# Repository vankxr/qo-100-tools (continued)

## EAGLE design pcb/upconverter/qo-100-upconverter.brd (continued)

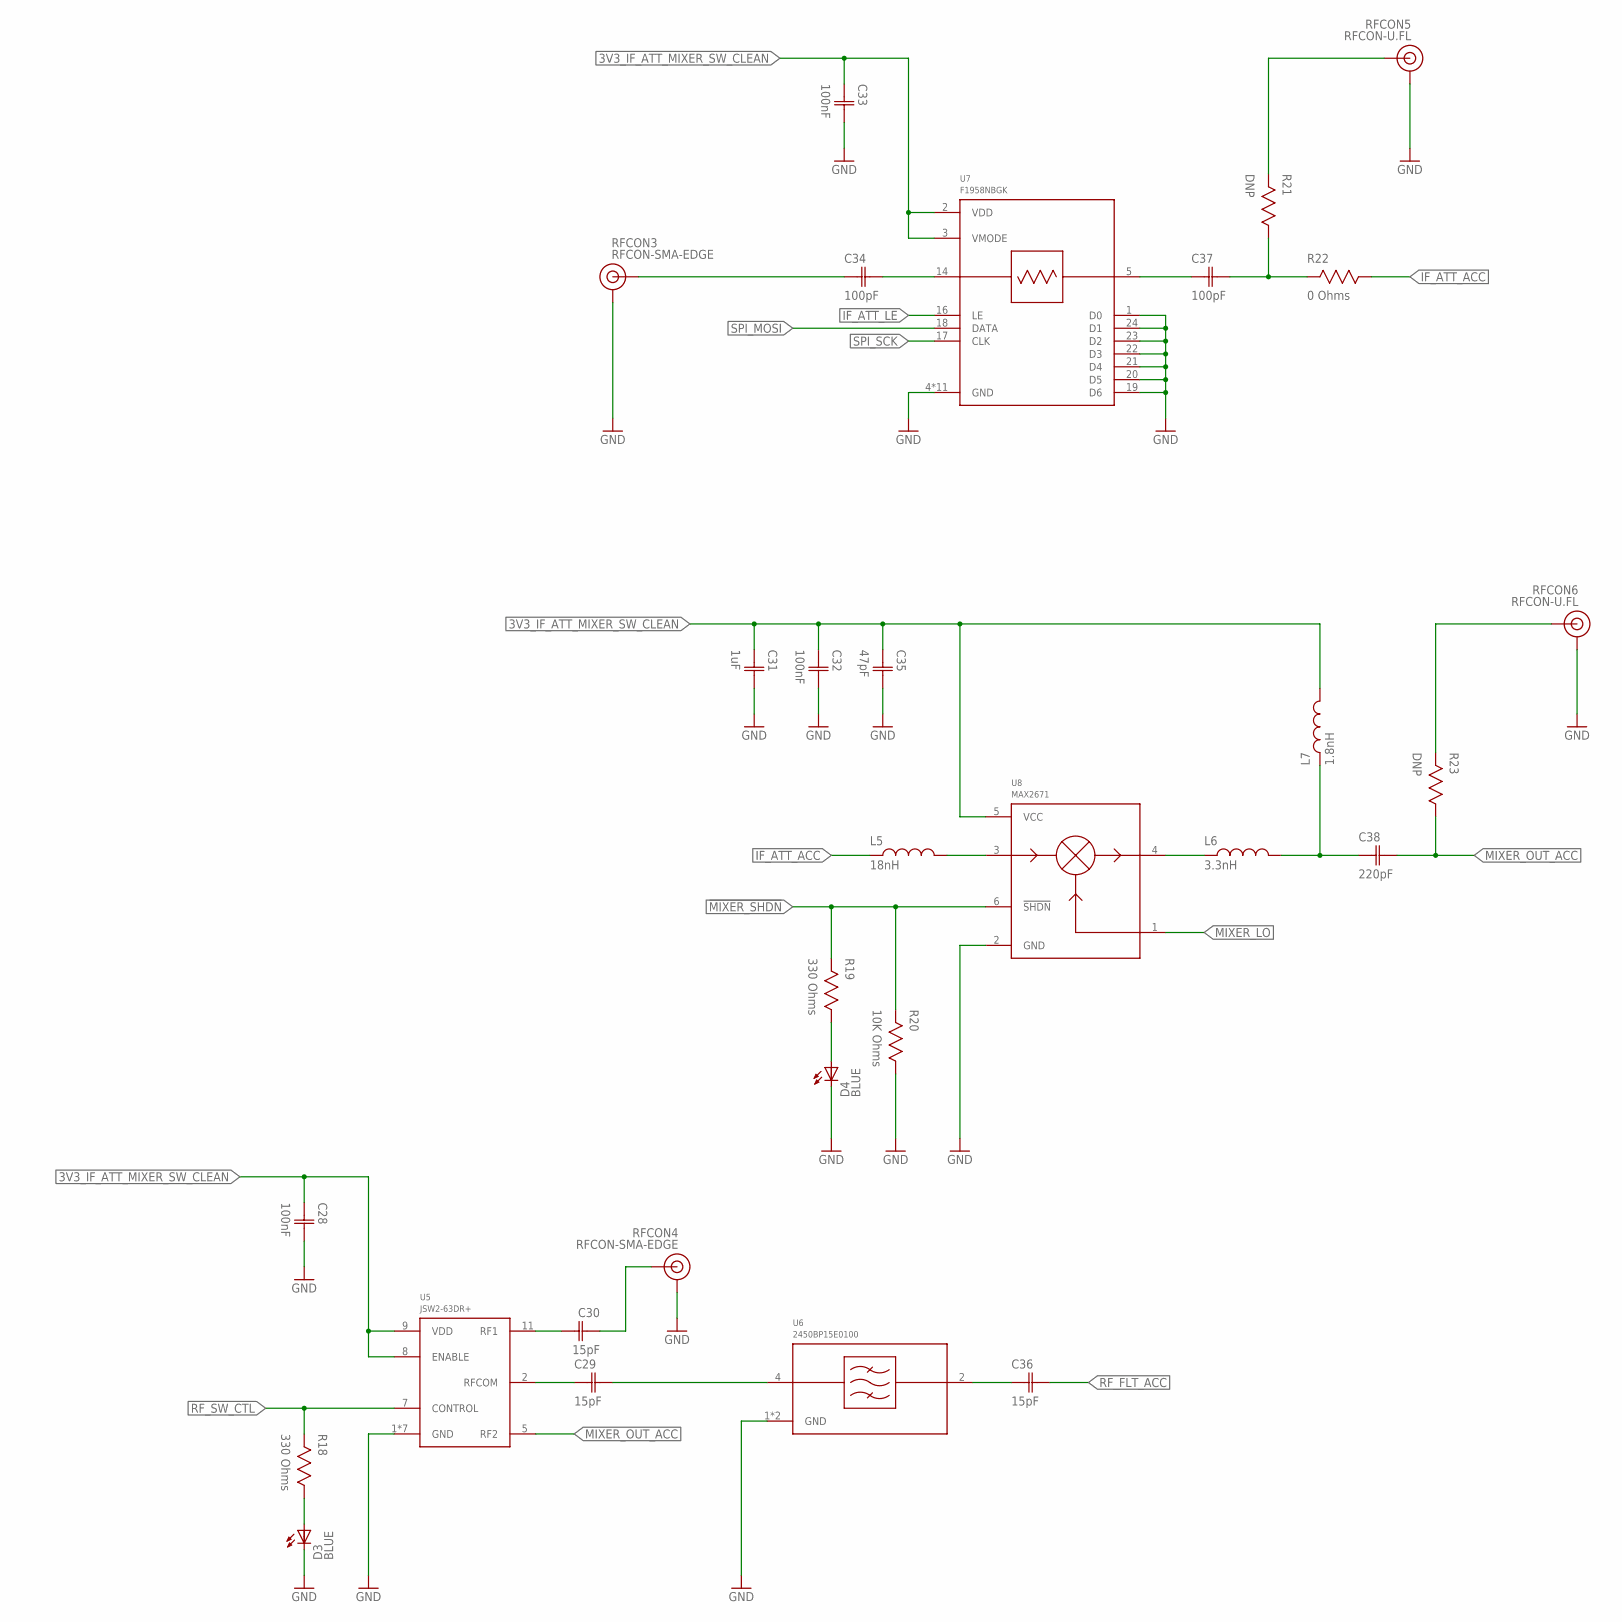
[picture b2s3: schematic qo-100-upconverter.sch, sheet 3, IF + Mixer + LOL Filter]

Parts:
C28, C32, C33: 100nF; CAP0603
C29, C30, C36: 15pF; CAP0603
C31: 1uF; CAP0603
C34, C37: 100pF; CAP0603
C35: 47pF; CAP0603
C38: 220pF; CAP0603
D3, D4: LED0603; 0603
L5: 18nH; IND0603
L6: 3.3nH; IND0603
L7: 1.8nH; IND0603
R18, R19: 330 Ohms; RES0603
R20: 10K Ohms; RES0603
R21, R23: DNP; RES0603
R22: 0 Ohms; RES0603
RFCON3, RFCON4: RFCON-SMA-EDGE; SMA-EDGE
RFCON5, RFCON6: RFCON-U.FL; U.FL
U5: JSW2-63DR+; MT1818
U6: 2450BP15E0100
U7: F1958NBGK; QFN24_2
U8: MAX2671; SOT23-6

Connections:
3V3_IF_ATT_MIXER_SW_CLEAN: C28.1 (C1), C31.1 (C1), C32.1 (C1), C33.1 (C1), C35.1 (C1), L7.2, U5.8 (ENABLE), U5.9 (VDD), U7.2 (VDD), U7.3 (VMODE), U8.5 (VCC); also elsewhere on the board
!MIXER_SHDN: R19.2, R20.2, U8.6 (!SHDN); also elsewhere on the board
GND: C28.2 (C2), C31.2 (C2), C32.2 (C2), C33.2 (C2), C35.2 (C2), D3.C, D4.C, R20.1, RFCON3.GND@0 (GND), RFCON3.GND@1 (GND), RFCON3.GND@2 (GND), RFCON3.GND@3 (GND), RFCON4.GND@0 (GND), RFCON4.GND@1 (GND), RFCON4.GND@2 (GND), RFCON4.GND@3 (GND), RFCON5.P$1 (GND), RFCON5.P$2 (GND), RFCON6.P$1 (GND), RFCON6.P$2 (GND), U5.1 (GND), U5.3 (GND), U5.4 (GND), U5.6 (GND), U5.10 (GND), U5.12 (GND), U5.17 (GND), U6.1 (GND), U6.3 (GND), U7.1 (D0), U7.4 (GND), U7.6 (GND), U7.7 (GND), U7.8 (GND), U7.9 (GND), U7.10 (GND), U7.11 (GND), U7.12 (GND), U7.13 (GND), U7.15 (GND), U7.19 (D6), U7.20 (D5), U7.21 (D4), U7.22 (D3), U7.23 (D2), U7.24 (D1), U7.25 (GND), U8.2 (GND); also elsewhere on the board
IF_ATT_ACC: L5.1, R22.1
IF_ATT_ACC_PROBE: C37.2 (C2), R21.1, R22.2
IF_ATT_DCC: C37.1 (C1), U7.5 (RF1)
IF_ATT_LE: U7.16 (LE); also elsewhere on the board
IF_IN_ACC: C34.2 (C2), U7.14 (RF2)
IF_IN_DCC: C34.1 (C1), RFCON3.SIG (SIGNAL)
MIXER_IN_DCC: L5.2, U8.3 (IFIN)
MIXER_LO: U8.1 (LO); also elsewhere on the board
MIXER_OUT_ACC: C38.2 (C2), R23.1, U5.5 (RF2)
MIXER_OUT_DCC: L6.1, U8.4 (RFOUT)
unnamed: D4.A, R19.1
unnamed: C38.1 (C1), L6.2, L7.1
unnamed: D3.A, R18.1
unnamed: R21.2, RFCON5.P$3 (SIGNAL)
unnamed: R23.2, RFCON6.P$3 (SIGNAL)
RF_FLT_ACC: C36.2 (C2); also elsewhere on the board
RF_IN_ACC: C30.2 (C2), U5.11 (RF1)
RF_IN_DCC: C30.1 (C1), RFCON4.SIG (SIGNAL)
RF_SEL_ACC: C29.2 (C2), U6.4 (RFIN)
RF_SEL_DCC: C29.1 (C1), U5.2 (RFCOM)
RF_SEL_FILT_DCC: C36.1 (C1), U6.2 (RFOUT)
RF_SW_CTL: R18.2, U5.7 (CONTROL); also elsewhere on the board
SPI_MOSI: U7.18 (DATA); also elsewhere on the board
SPI_SCK: U7.17 (CLK); also elsewhere on the board

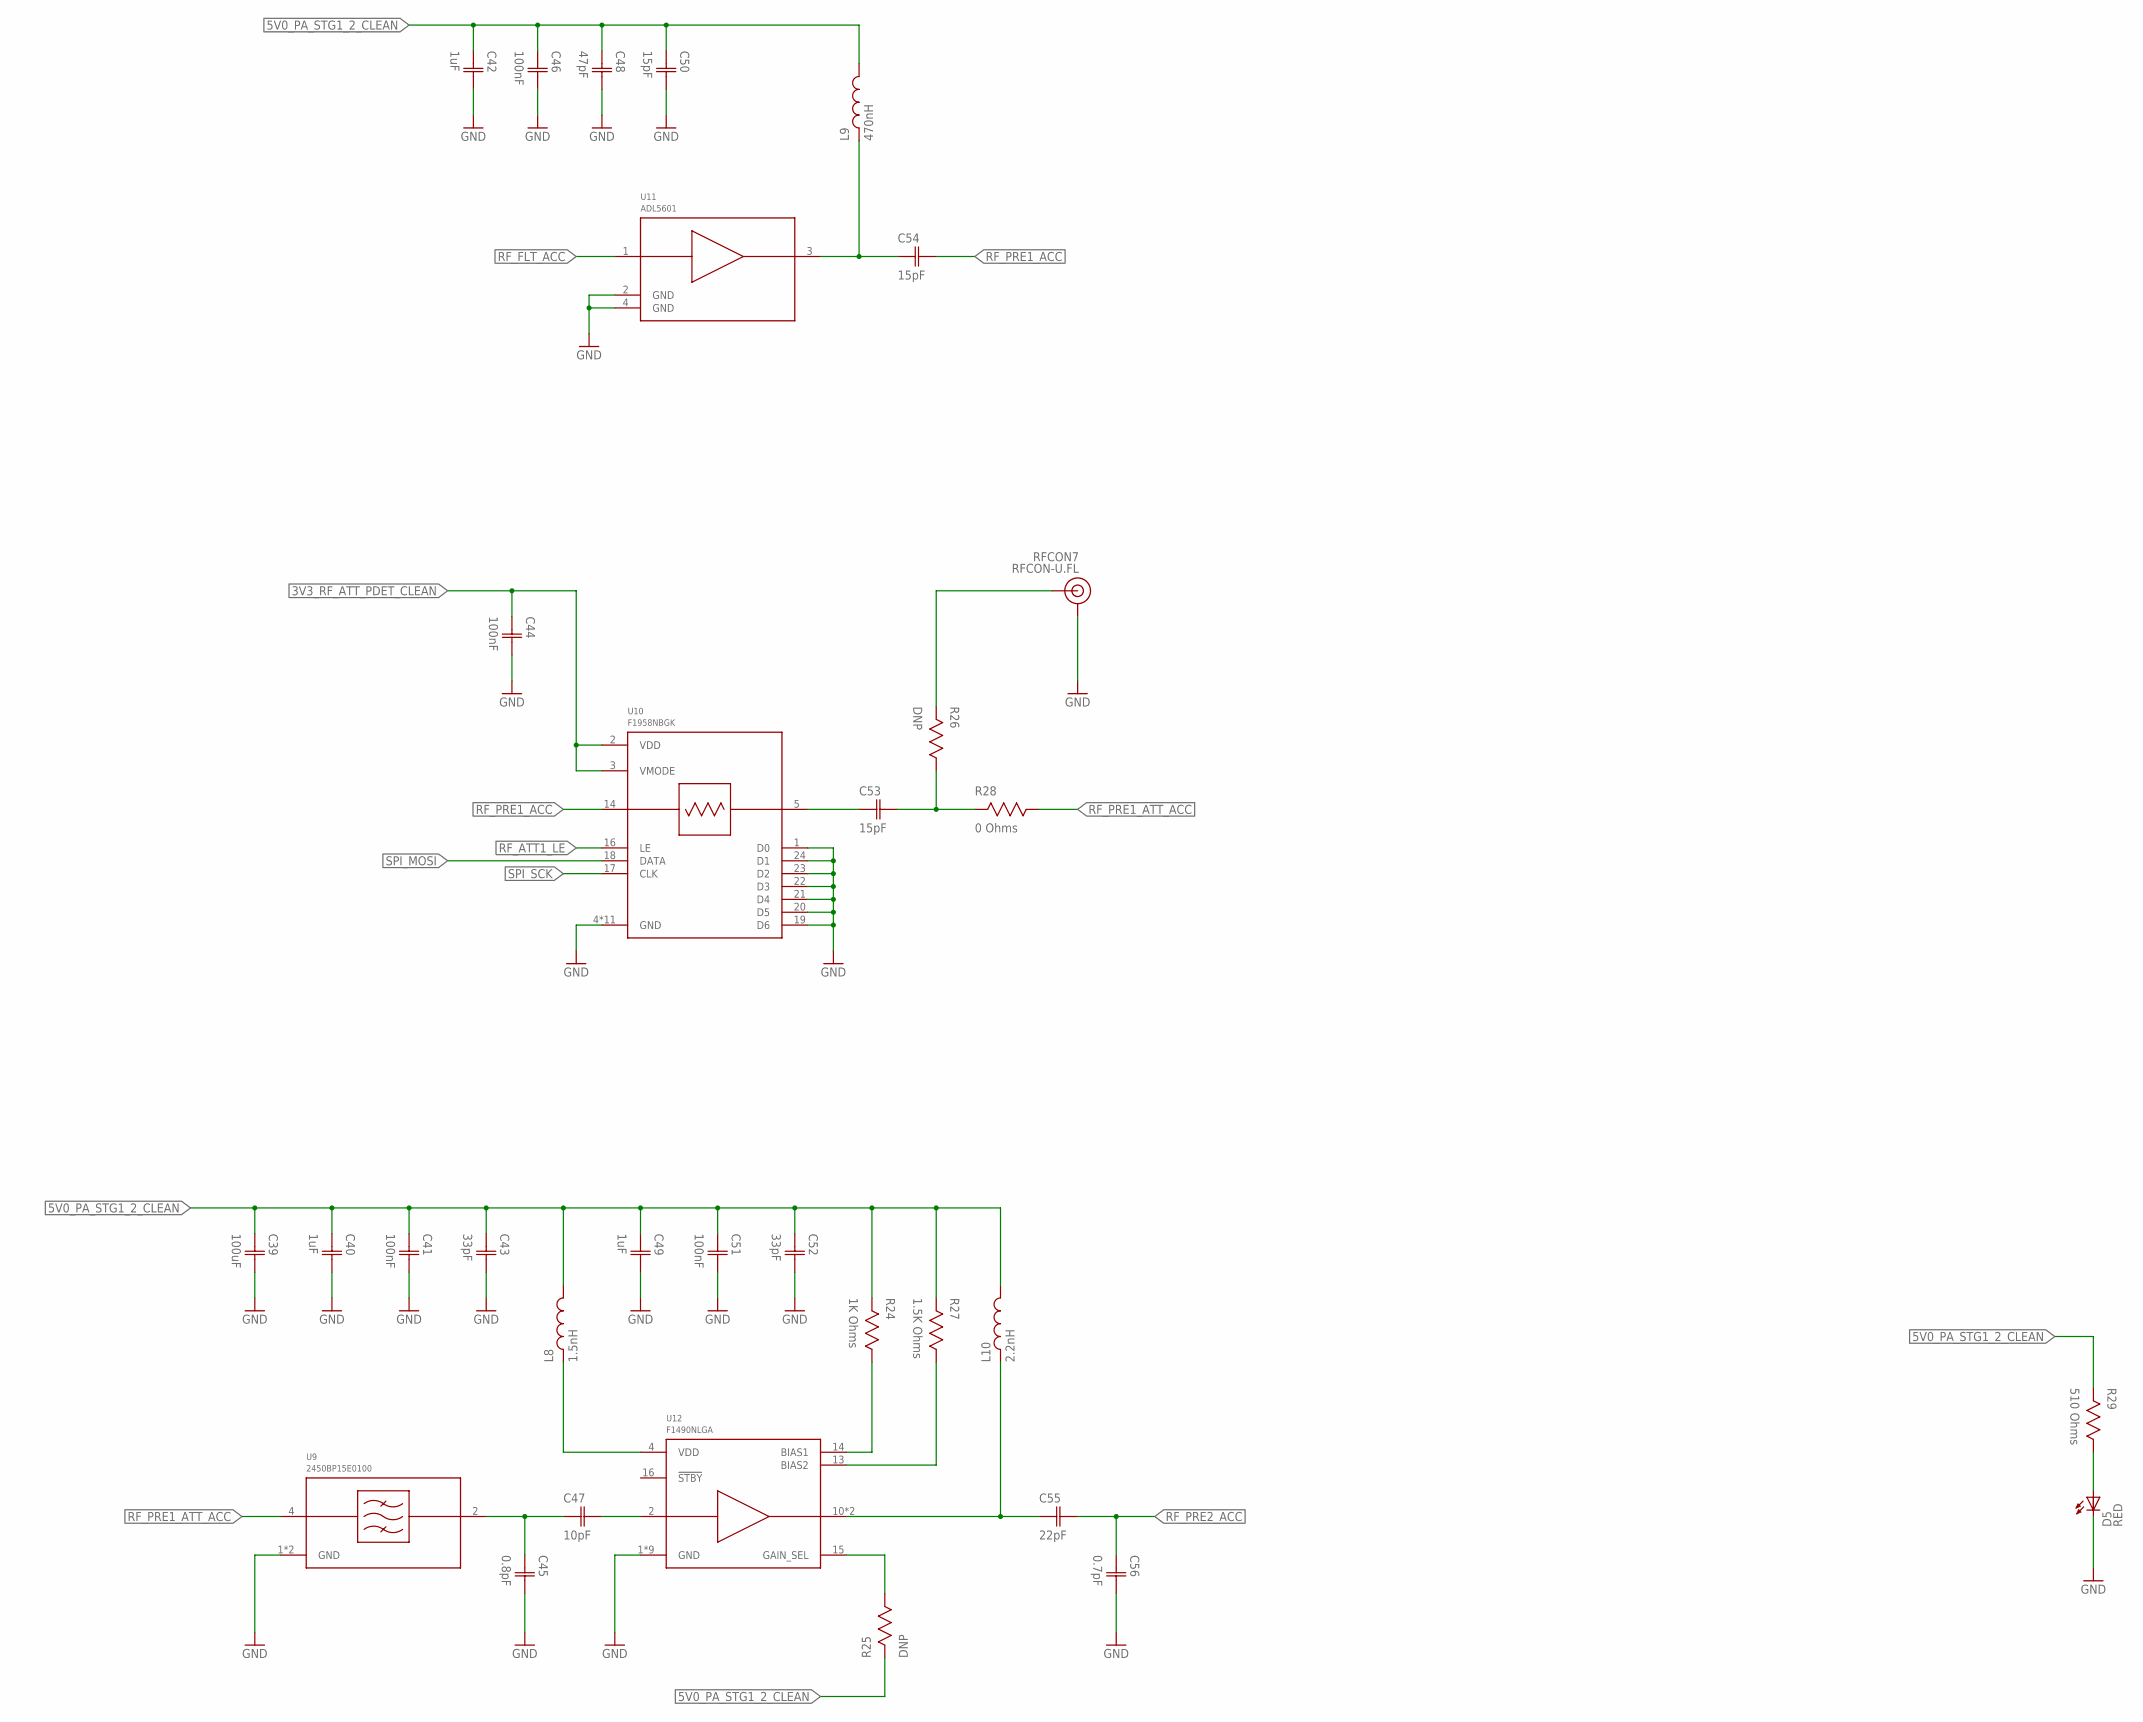
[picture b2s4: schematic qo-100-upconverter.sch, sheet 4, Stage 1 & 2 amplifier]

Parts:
C39: 100uF; CAP1206
C40, C42, C49: 1uF; CAP0603
C41, C44, C46, C51: 100nF; CAP0603
C43, C52: 33pF; CAP0603
C45: 0.8pF; CAP0603
C47: 10pF; CAP0603
C48: 47pF; CAP0603
C50, C53, C54: 15pF; CAP0603
C55: 22pF; CAP0603
C56: 0.7pF; CAP0603
D5: LED0603; 0603
L8: 1.5nH; IND0603
L9: 470nH; IND0603
L10: 2.2nH; IND0603
R24: 1K Ohms; RES0603
R25, R26: DNP; RES0603
R27: 1.5K Ohms; RES0603
R28: 0 Ohms; RES0603
R29: 510 Ohms; RES0603
RFCON7: RFCON-U.FL; U.FL
U9: 2450BP15E0100
U10: F1958NBGK; QFN24_2
U11: ADL5601; SOT89
U12: F1490NLGA; QFN16

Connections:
3V3_RF_ATT_PDET_CLEAN: C44.1 (C1), U10.2 (VDD), U10.3 (VMODE); also elsewhere on the board
5V0_PA_STG1_2_CLEAN: C39.1 (C1), C40.1 (C1), C41.1 (C1), C42.1 (C1), C43.1 (C1), C46.1 (C1), C48.1 (C1), C49.1 (C1), C50.1 (C1), C51.1 (C1), C52.1 (C1), L8.2, L9.2, L10.2, R24.2, R25.2, R27.2, R29.2; also elsewhere on the board
GND: C39.2 (C2), C40.2 (C2), C41.2 (C2), C42.2 (C2), C43.2 (C2), C44.2 (C2), C45.2 (C2), C46.2 (C2), C48.2 (C2), C49.2 (C2), C50.2 (C2), C51.2 (C2), C52.2 (C2), C56.2 (C2), D5.C, RFCON7.P$1 (GND), RFCON7.P$2 (GND), U9.1 (GND), U9.3 (GND), U10.1 (D0), U10.4 (GND), U10.6 (GND), U10.7 (GND), U10.8 (GND), U10.9 (GND), U10.10 (GND), U10.11 (GND), U10.12 (GND), U10.13 (GND), U10.15 (GND), U10.19 (D6), U10.20 (D5), U10.21 (D4), U10.22 (D3), U10.23 (D2), U10.24 (D1), U10.25 (GND), U11.2 (GND), U11.4 (GND), U12.1 (GND), U12.3 (GND), U12.5 (GND), U12.6 (GND), U12.7 (GND), U12.8 (GND), U12.9 (GND), U12.12 (GND), U12.17 (GND); also elsewhere on the board
unnamed: R25.1, U12.15 (GAIN_SEL)
unnamed: L8.1, U12.4 (VDD)
unnamed: R24.1, U12.14 (BIAS1)
unnamed: R27.1, U12.13 (BIAS2)
unnamed: D5.A, R29.1
unnamed: C47.2 (C2), U12.2 (RFIN)
unnamed: R26.2, RFCON7.P$3 (SIGNAL)
RF_ATT1_LE: U10.16 (LE); also elsewhere on the board
RF_FLT_ACC: U11.1 (RFIN); also elsewhere on the board
RF_PRE1_ACC: C54.2 (C2), U10.14 (RF2)
RF_PRE1_ATT_ACC: R28.1, U9.4 (RFIN)
RF_PRE1_ATT_ACC_PROBE: C53.2 (C2), R26.1, R28.2
RF_PRE1_ATT_DCC: C53.1 (C1), U10.5 (RF1)
RF_PRE1_ATT_FLT_ACC: C45.1 (C1), C47.1 (C1), U9.2 (RFOUT)
RF_PRE1_DCC: C54.1 (C1), L9.1, U11.3 (RFOUT)
RF_PRE2_ACC: C55.2 (C2), C56.1 (C1); also elsewhere on the board
RF_PRE2_DCC: C55.1 (C1), L10.1, U12.10 (RFOUT), U12.11 (RFOUT)
SPI_MOSI: U10.18 (DATA); also elsewhere on the board
SPI_SCK: U10.17 (CLK); also elsewhere on the board

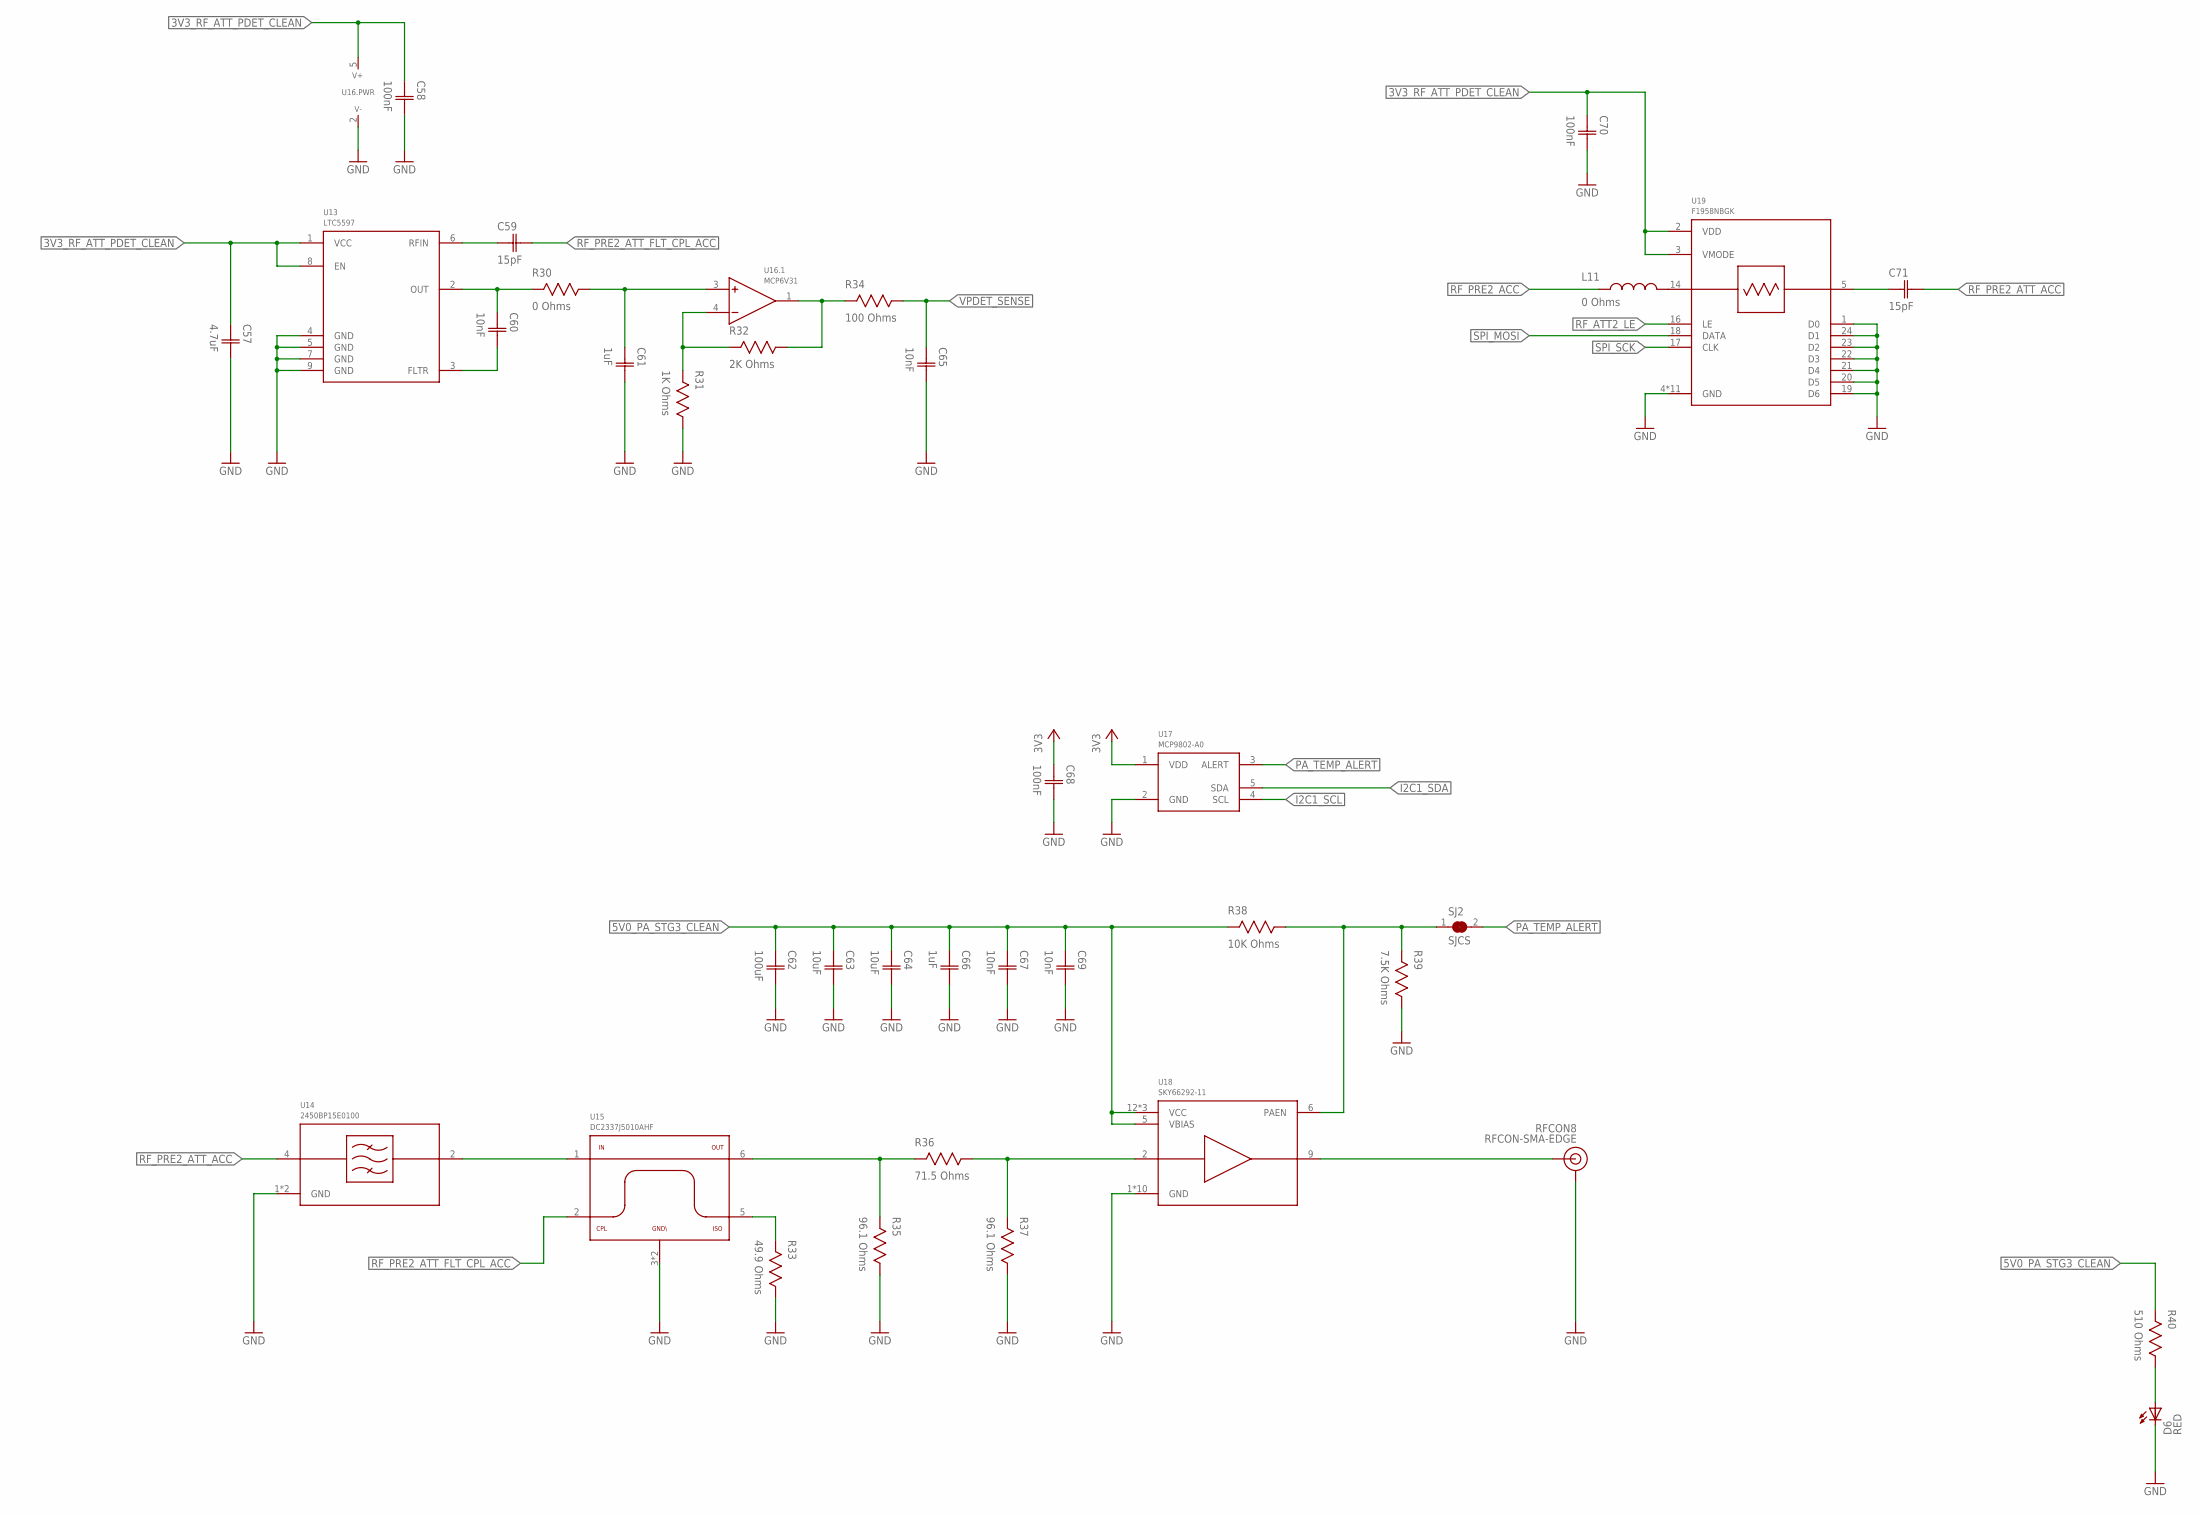
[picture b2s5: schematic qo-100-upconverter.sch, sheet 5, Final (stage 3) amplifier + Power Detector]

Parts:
C57: 4.7uF; CAP0603
C58, C68, C70: 100nF; CAP0603
C59, C71: 15pF; CAP0603
C60, C65, C67, C69: 10nF; CAP0603
C61, C66: 1uF; CAP0603
C62: 100uF; CAP1206
C63, C64: 10uF; CAP0603
D6: LED0603; 0603
L11: 0 Ohms; IND0603
R30: 0 Ohms; RES0603
R31: 1K Ohms; RES0603
R32: 2K Ohms; RES0603
R33: 49.9 Ohms; RES0603
R34: 100 Ohms; RES0603
R35, R37: 96.1 Ohms; RES0603
R36: 71.5 Ohms; RES0603
R38: 10K Ohms; RES0603
R39: 7.5K Ohms; RES0603
R40: 510 Ohms; RES0603
RFCON8: RFCON-SMA-EDGE; SMA-EDGE
SJ2: SJCS; SJC_S
U13: LTC5597; DFN8_2X2
U14: 2450BP15E0100
U15: DC2337J5010AHF
U16: MCP6V31; SOT23-5
U17: MCP9802-A0; SOT23-5
U18: SKY66292-11
U19: F1958NBGK; QFN24_2

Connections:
3V3: C68.1 (C1), U17.1 (VDD); also elsewhere on the board
3V3_RF_ATT_PDET_CLEAN: C57.1 (C1), C58.1 (C1), C70.1 (C1), U13.1 (VCC), U13.8 (EN), U16.5 (V+), U19.2 (VDD), U19.3 (VMODE); also elsewhere on the board
5V0_PA_STG3_CLEAN: C62.1 (C1), C63.1 (C1), C64.1 (C1), C66.1 (C1), C67.1 (C1), C69.1 (C1), R38.2, R40.2, U18.5 (VBIAS), U18.12 (VCC), U18.14 (VCC), U18.16 (VCC); also elsewhere on the board
GND: C57.2 (C2), C58.2 (C2), C61.2 (C2), C62.2 (C2), C63.2 (C2), C64.2 (C2), C65.2 (C2), C66.2 (C2), C67.2 (C2), C68.2 (C2), C69.2 (C2), C70.2 (C2), D6.C, R31.1, R33.1, R35.1, R37.1, R39.1, RFCON8.GND@0 (GND), RFCON8.GND@1 (GND), RFCON8.GND@2 (GND), RFCON8.GND@3 (GND), U13.4 (GND), U13.5 (GND), U13.7 (GND), U13.9 (GND), U14.1 (GND), U14.3 (GND), U15.3 (GND), U15.4 (GND), U16.2 (V-), U17.2 (GND), U18.1 (GND), U18.3 (GND), U18.4 (GND), U18.7 (GND), U18.8 (GND), U18.10 (GND), U18.11 (GND), U18.13 (GND), U18.15 (GND), U18.17 (GND), U19.1 (D0), U19.4 (GND), U19.6 (GND), U19.7 (GND), U19.8 (GND), U19.9 (GND), U19.10 (GND), U19.11 (GND), U19.12 (GND), U19.13 (GND), U19.15 (GND), U19.19 (D6), U19.20 (D5), U19.21 (D4), U19.22 (D3), U19.23 (D2), U19.24 (D1), U19.25 (GND); also elsewhere on the board
I2C1_SCL: U17.4 (SCL); also elsewhere on the board
I2C1_SDA: U17.5 (SDA); also elsewhere on the board
unnamed: D6.A, R40.1
unnamed: R31.2, R32.2, U16.4 (-IN)
unnamed: L11.2, U19.14 (RF2)
unnamed: R33.2, U15.5 (ISOLATED)
unnamed: C59.1 (C1), U13.6 (RFIN)
unnamed: C60.2 (C2), U13.3 (FLTR)
PA3_EN: R38.1, R39.2, SJ2.1, U18.6 (PAEN)
PA_TEMP_ALERT: SJ2.2, U17.3 (ALERT)
RF_ATT2_LE: U19.16 (LE); also elsewhere on the board
RF_FINAL_ACC: RFCON8.SIG (SIGNAL), U18.9 (RFOUT)
RF_PRE2_ACC: L11.1; also elsewhere on the board
RF_PRE2_ATT_ACC: C71.2 (C2), U14.4 (RFIN)
RF_PRE2_ATT_DCC: C71.1 (C1), U19.5 (RF1)
RF_PRE2_ATT_FLT_ACC: U14.2 (RFOUT), U15.1 (IN)
RF_PRE2_ATT_FLT_CPL_ACC: C59.2 (C2), U15.2 (COUPLED)
RF_PRE2_ATT_FLT_THRU_ACC: R35.2, R36.2, U15.6 (OUT)
RF_PRE2_ATT_FLT_THRU_ACC_ATT: R36.1, R37.2, U18.2 (RFIN)
SPI_MOSI: U19.18 (DATA); also elsewhere on the board
SPI_SCK: U19.17 (CLK); also elsewhere on the board
VPDET_AMP: R32.1, R34.2, U16.1 (OUT)
VPDET_FLT: C61.1 (C1), R30.1, U16.3 (+IN)
VPDET_RAW: C60.1 (C1), R30.2, U13.2 (OUT)
VPDET_SENSE: C65.1 (C1), R34.1; also elsewhere on the board

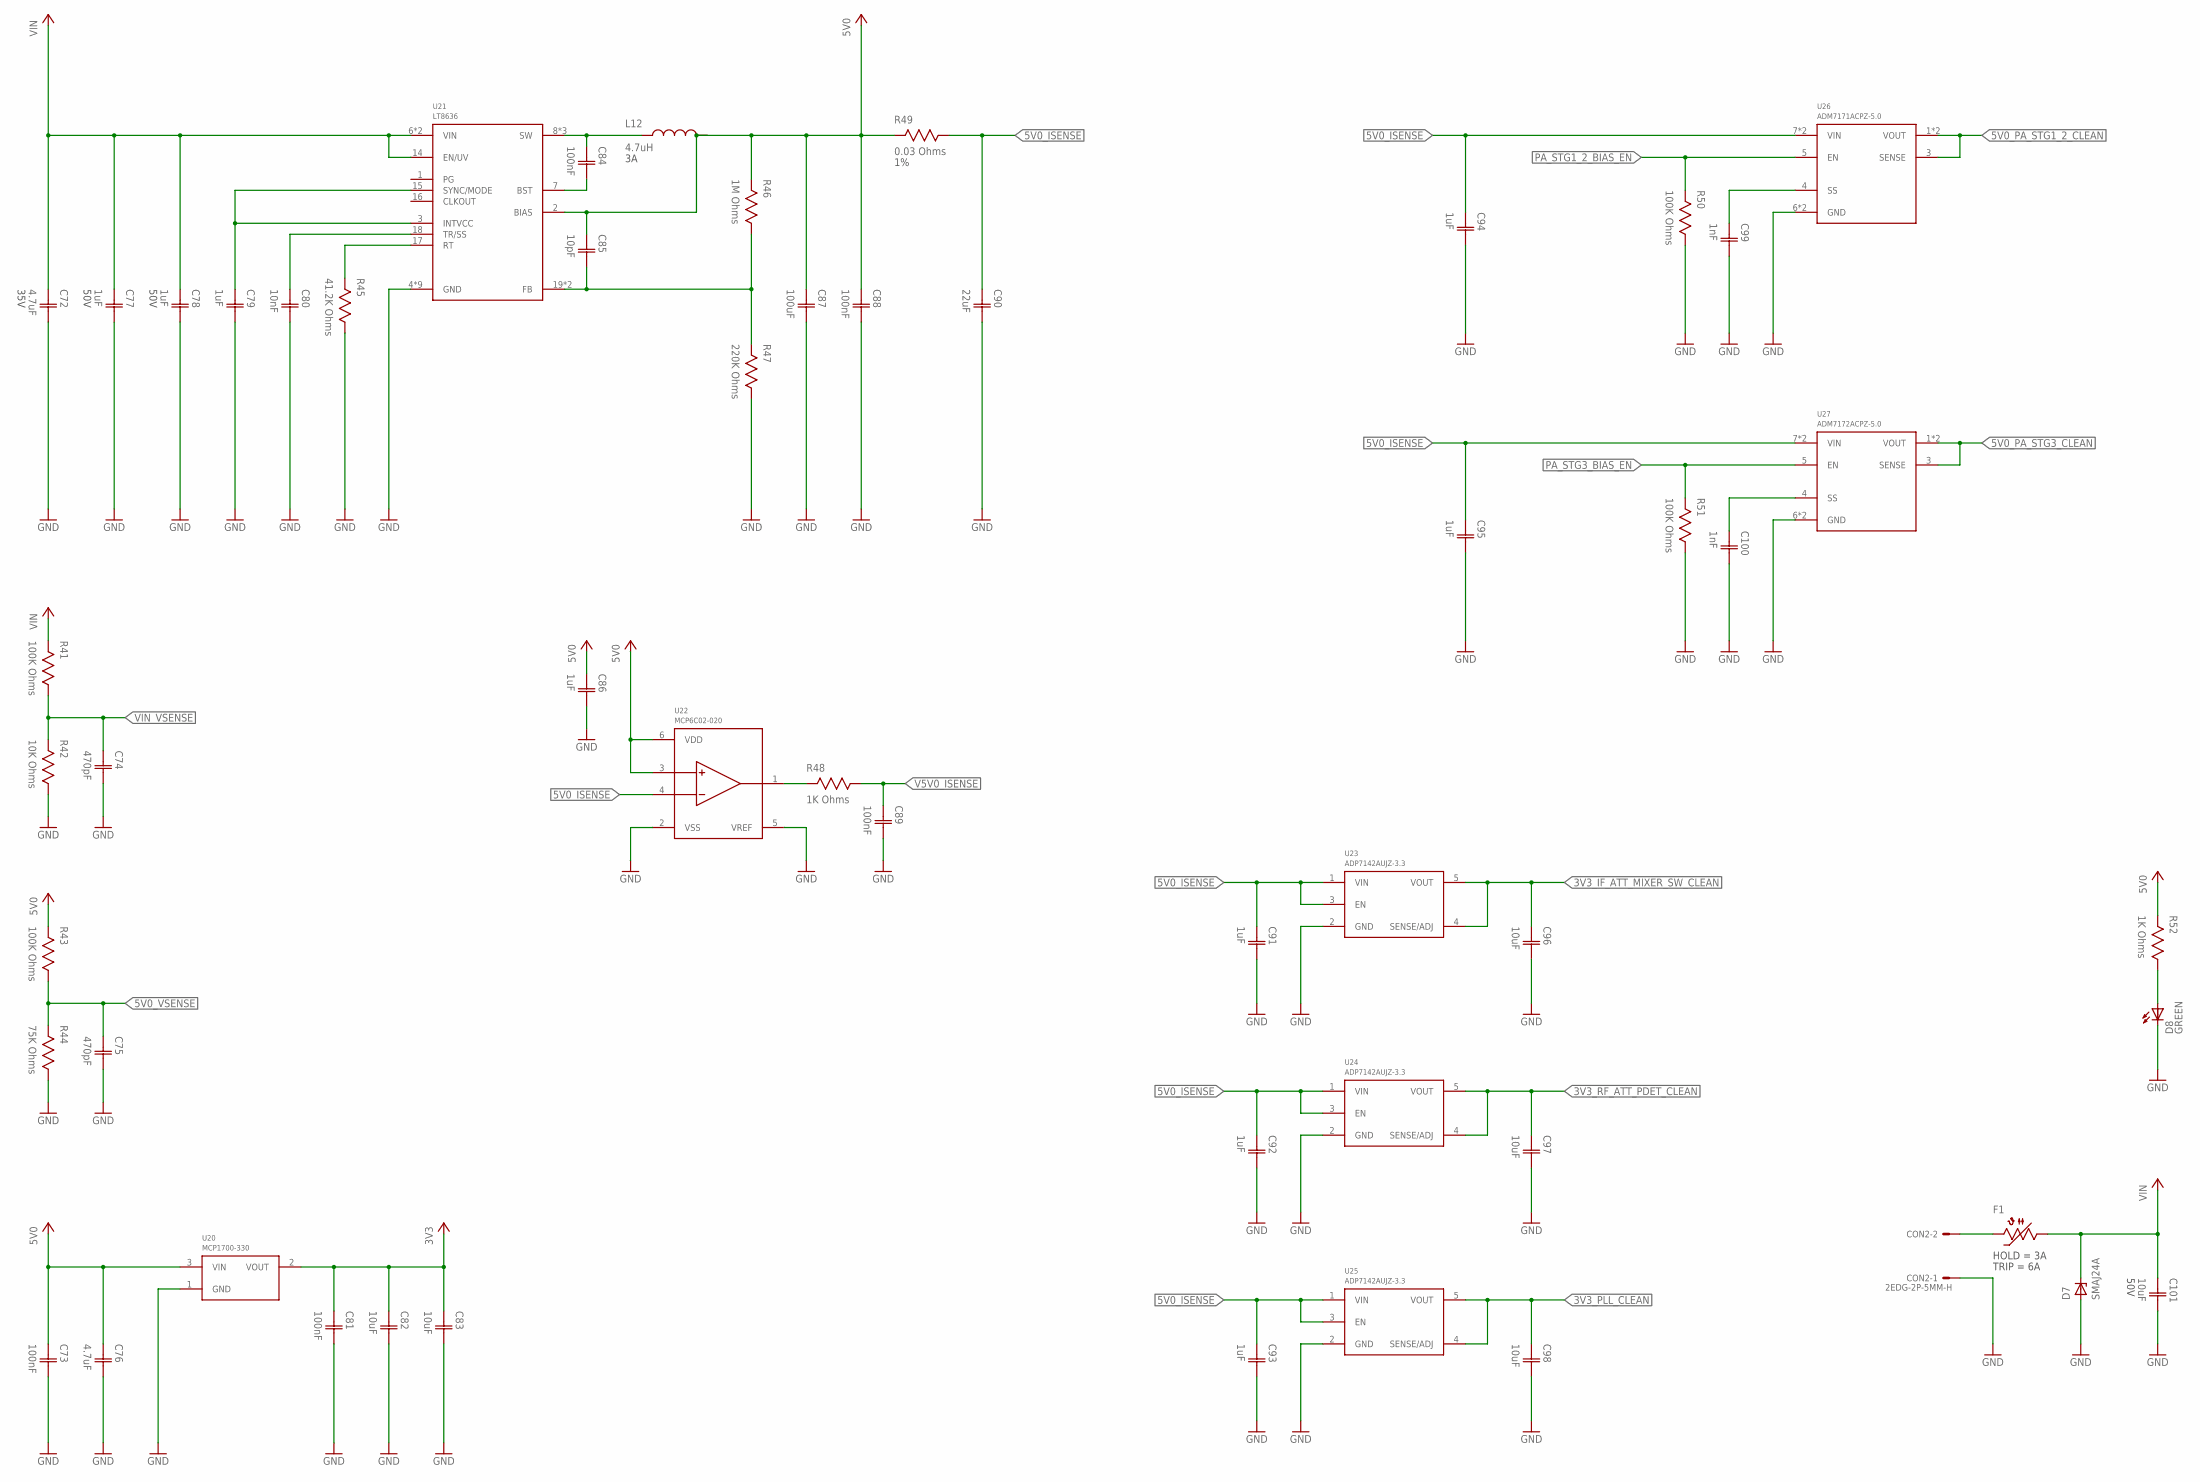
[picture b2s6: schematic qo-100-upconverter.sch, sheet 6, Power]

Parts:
C72: 4.7uF; CAP0603; VOLTAGE 35V
C73, C81, C84, C88, C89: 100nF; CAP0603
C74, C75: 470pF; CAP0603
C76: 4.7uF; CAP0603
C77, C78: 1uF; CAP0603; VOLTAGE 50V
C79, C86, C91, C92, C93, C94, C95: 1uF; CAP0603
C80: 10nF; CAP0603
C82, C83, C96, C97, C98: 10uF; CAP0603
C85: 10pF; CAP0603
C87: 100uF; CAP1206
C90: 22uF; CAP1206
C99, C100: 1nF; CAP0603
C101: 10uF; CAP1206; VOLTAGE 50V
CON2: 2EDG-2P-5MM-H
D7: SMAJ24A; DO214AC
D8: LED0603; 0603
F1: 2.6A Hold; 1206
L12: 4.7uH; IND0606
R41, R43, R50, R51: 100K Ohms; RES0603
R42: 10K Ohms; RES0603
R44: 75K Ohms; RES0603
R45: 41.2K Ohms; RES0603
R46: 1M Ohms; RES0603
R47: 220K Ohms; RES0603
R48, R52: 1K Ohms; RES0603
R49: 0.03 Ohms; RES1206; TOLERANCE 1%
U20: MCP1700-330; SOT23
U21: LT8636; QFN20_ASYM_3X4_CORNER
U22: MCP6C02-020; SOT23-6
U23, U24, U25: ADP7142AUJZ-3.3; SOT23-5
U26: ADM7171ACPZ-5.0; LFCSP8_3X3
U27: ADM7172ACPZ-5.0; LFCSP8_3X3

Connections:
3V3: C81.1 (C1), C82.1 (C1), C83.1 (C1), U20.2 (VOUT); also elsewhere on the board
3V3_IF_ATT_MIXER_SW_CLEAN: C96.1 (C1), U23.4 (SENSE/ADJ), U23.5 (VOUT); also elsewhere on the board
3V3_PLL_CLEAN: C98.1 (C1), U25.4 (SENSE/ADJ), U25.5 (VOUT); also elsewhere on the board
3V3_RF_ATT_PDET_CLEAN: C97.1 (C1), U24.4 (SENSE/ADJ), U24.5 (VOUT); also elsewhere on the board
5V0: C73.1 (C1), C76.1 (C1), C85.1 (C1), C86.1 (C1), C87.1 (C1), C88.1 (C1), L12.2, R43.2, R46.2, R49.2, R52.2, U20.3 (VIN), U21.2 (BIAS), U22.3 (VIP), U22.6 (VDD)
5V0_BST: C84.2 (C2), U21.7 (BST)
5V0_FB: C85.2 (C2), R46.1, R47.2, U21.19 (FB), U21.20 (FB)
5V0_INTVCC: C79.1 (C1), U21.3 (INTVCC), U21.15 (SYNC/MODE)
5V0_ISENSE: C90.1 (C1), C91.1 (C1), C92.1 (C1), C93.1 (C1), C94.1 (C1), C95.1 (C1), R49.1, U22.4 (VIM), U23.1 (VIN), U23.3 (EN), U24.1 (VIN), U24.3 (EN), U25.1 (VIN), U25.3 (EN), U26.7 (VIN), U26.8 (VIN), U27.7 (VIN), U27.8 (VIN)
5V0_PA_STG1_2_CLEAN: U26.1 (VOUT), U26.2 (VOUT), U26.3 (SENSE); also elsewhere on the board
5V0_PA_STG3_CLEAN: U27.1 (VOUT), U27.2 (VOUT), U27.3 (SENSE); also elsewhere on the board
5V0_RT: R45.2, U21.17 (RT)
5V0_SS: C80.1 (C1), U21.18 (TR/SS)
5V0_SW: C84.1 (C1), L12.1, U21.8 (SW), U21.9 (SW), U21.10 (SW)
5V0_VSENSE: C75.1 (C1), R43.1, R44.2; also elsewhere on the board
GND: C72.2 (C2), C73.2 (C2), C74.2 (C2), C75.2 (C2), C76.2 (C2), C77.2 (C2), C78.2 (C2), C79.2 (C2), C80.2 (C2), C81.2 (C2), C82.2 (C2), C83.2 (C2), C86.2 (C2), C87.2 (C2), C88.2 (C2), C89.2 (C2), C90.2 (C2), C91.2 (C2), C92.2 (C2), C93.2 (C2), C94.2 (C2), C95.2 (C2), C96.2 (C2), C97.2 (C2), C98.2 (C2), C99.2 (C2), C100.2 (C2), C101.2 (C2), CON2.P$1, D7.A, D8.C, R42.1, R44.1, R45.1, R47.1, R50.1, R51.1, U20.1 (GND), U21.4 (GND), U21.5 (GND), U21.12 (GND), U21.13 (GND), U21.21 (GND), U21.M1 (GND), U21.M2 (GND), U21.M3 (GND), U21.M4 (GND), U22.2 (VSS), U22.5 (VREF), U23.2 (GND), U24.2 (GND), U25.2 (GND), U26.6 (GND), U26.9 (GND), U27.6 (GND), U27.9 (GND); also elsewhere on the board
unnamed: C100.1 (C1), U27.4 (SS)
unnamed: CON2.P$2, F1.2
unnamed: C99.1 (C1), U26.4 (SS)
unnamed: D8.A, R52.1
PA_STG1_2_BIAS_EN: R50.2, U26.5 (EN); also elsewhere on the board
PA_STG3_BIAS_EN: R51.2, U27.5 (EN); also elsewhere on the board
V5V0_ISENSE: C89.1 (C1), R48.1; also elsewhere on the board
V5V0_ISENSE-AMP: R48.2, U22.1 (VOUT)
VIN: C72.1 (C1), C77.1 (C1), C78.1 (C1), C101.1 (C1), D7.C, F1.1, R41.2, U21.6 (VIN), U21.11 (VIN), U21.14 (EN/UV)
VIN_VSENSE: C74.1 (C1), R41.1, R42.2; also elsewhere on the board

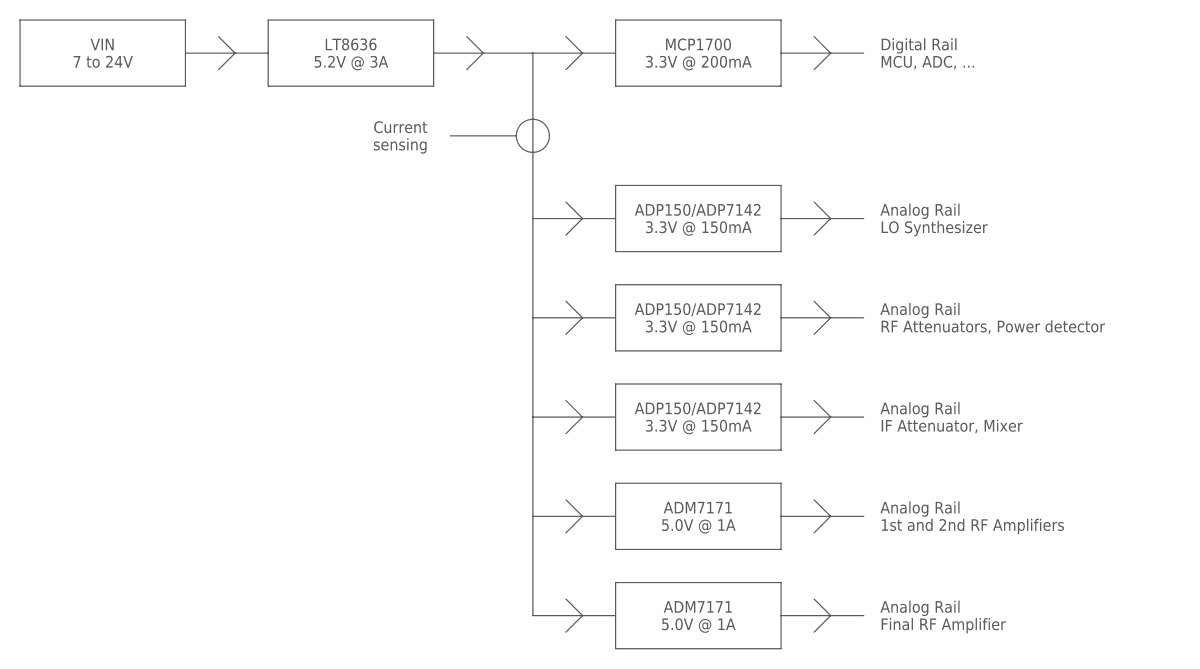
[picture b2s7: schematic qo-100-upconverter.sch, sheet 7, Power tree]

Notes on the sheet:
ADP150/ADP7142 3.3V @ 150mA
VIN 7 to 24V
LT8636 5.2V @ 3A
MCP1700 3.3V @ 200mA
Digital Rail MCU, ADC, ...
Analog Rail LO Synthesizer
Analog Rail RF Attenuators, Power detector
Analog Rail IF Attenuator, Mixer
ADM7171 5.0V @ 1A
Analog Rail 1st and 2nd RF Amplifiers
Analog Rail Final RF Amplifier
Current sensing

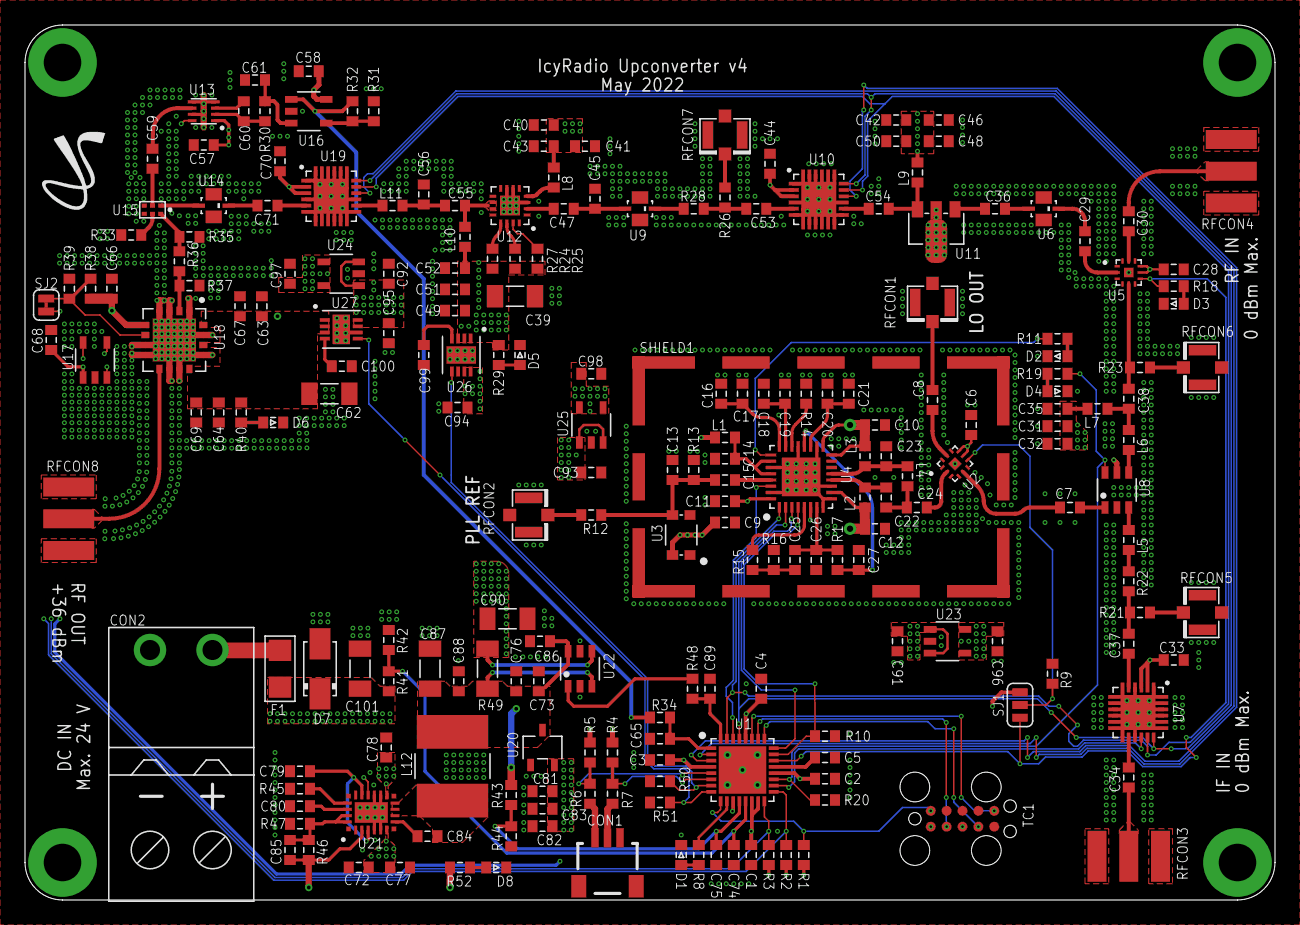
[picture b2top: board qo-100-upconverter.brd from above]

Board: 4 copper layers, 100.0 x 70.0 mm, 216 parts (0 on the bottom side), 125 nets.
